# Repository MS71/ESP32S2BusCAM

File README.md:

# ESP32S2BusCAM

Fetures:
* ESP32 S2/S3 Mini Modul mit und ohne PSRAM
* USB Micro Port
* JTAG Stecker
* ESP Prog Stecker
* Micro SDCard Slot
* 22 Pin Camera Stecker, Camera wird auf das ESP32 Modul geklappt
* Spannungs Regler für Ext Versorgung
* SPI/I2C Bus Stecker
* Support für Stereo Quad Camara
* 4 Pin OLED Display
* IR LEDs
* Debug LEDs

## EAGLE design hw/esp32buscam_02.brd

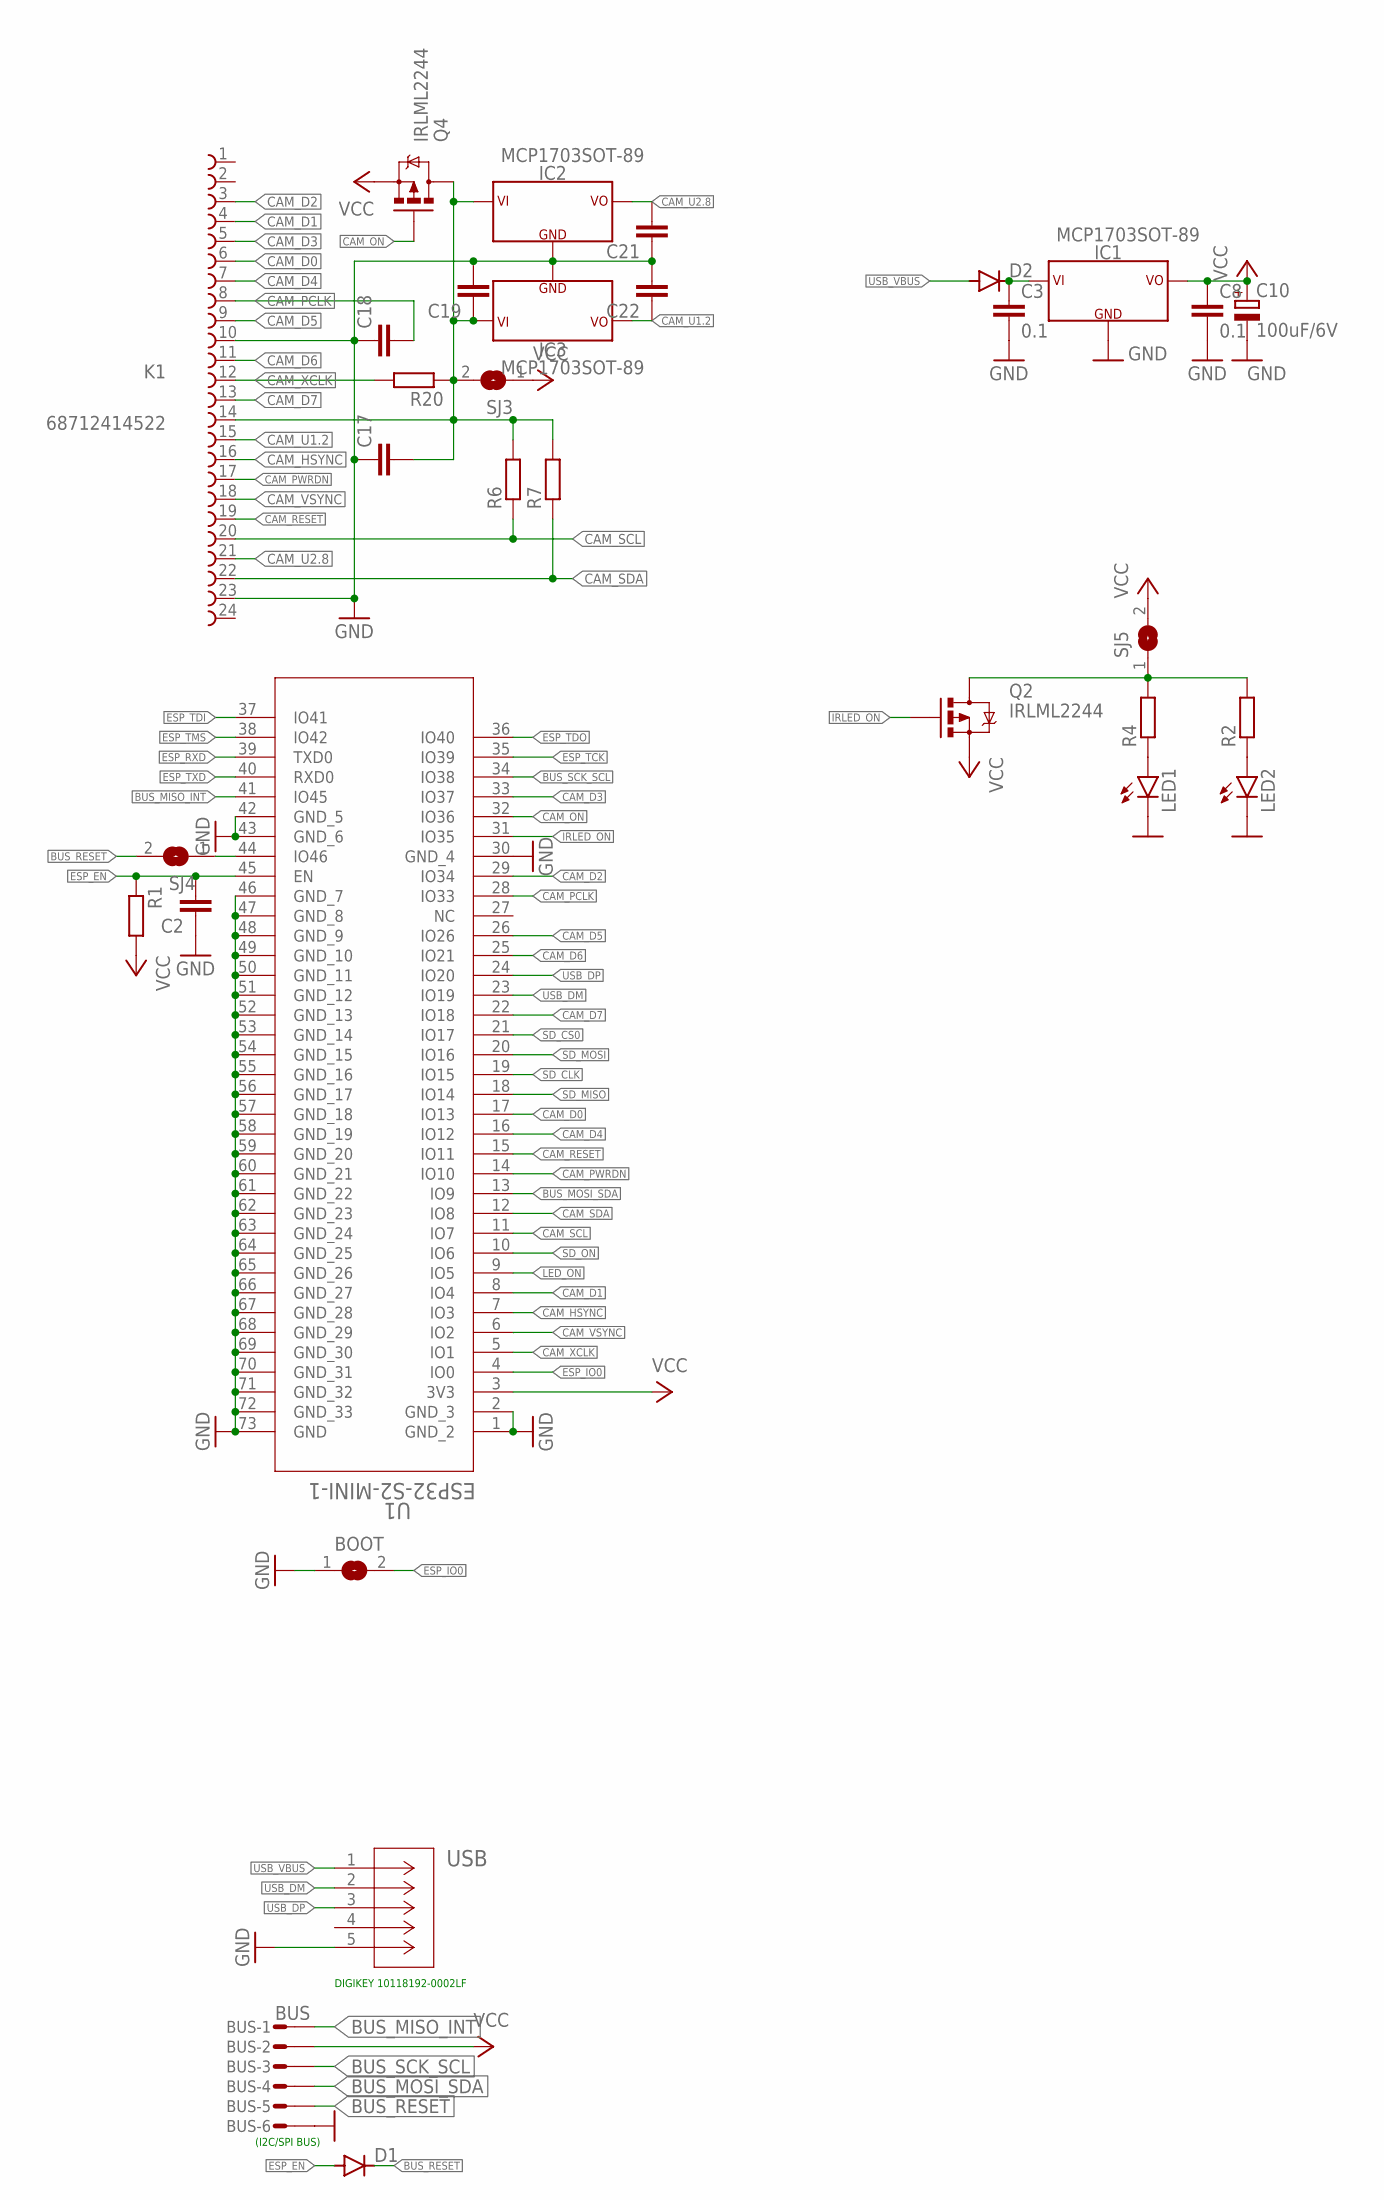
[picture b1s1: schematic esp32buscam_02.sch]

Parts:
BOOT: SJ
BUS: BUS; MICROMATCH-6SMD
C2, C17, C18, C19, C21, C22: C-EUC0603; C0603
C3, C8: 0.1; C0805
C10: 100uF/6V; B/3528-21R
D1, D2: DIODE-MINIMELF; MINIMELF
IC1, IC2, IC3: MCP1703SOT-89; SOT89
K1: 68712414522
LED1, LED2: LED5MM
Q2, Q4: IRLML2244; SOT23-3
R1, R6, R7, R20: R-EU_R0603; R0603
R2, R4: R-EU_R0402; R0402
SJ3, SJ4, SJ5: SJ
U1: ESP32-S2-MINI-1; QFN60_ESP32-S2-MINI-1_EXP
USB: 10118192-0002LF; CONN_10118192-0002LF_AMP

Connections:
BUS_MISO_INT: BUS.1, U1.41 (IO45)
BUS_MOSI_SDA: BUS.4, U1.13 (IO9)
BUS_RESET: BUS.5, D1.C, SJ4.2
BUS_SCK_SCL: BUS.3, U1.34 (IO38)
CAM_D0: K1.6, U1.17 (IO13)
CAM_D1: K1.4, U1.8 (IO4)
CAM_D2: K1.3, U1.29 (IO34)
CAM_D3: K1.5, U1.33 (IO37)
CAM_D4: K1.7, U1.16 (IO12)
CAM_D5: K1.9, U1.26 (IO26)
CAM_D6: K1.11, U1.25 (IO21)
CAM_D7: K1.13, U1.22 (IO18)
CAM_HSYNC: K1.16, U1.7 (IO3)
CAM_ON: Q4.1 (G), U1.32 (IO36)
CAM_PCLK: C18.2, K1.8, U1.28 (IO33)
CAM_PWRDN: K1.17, U1.14 (IO10)
CAM_RESET: K1.19, U1.15 (IO11)
CAM_SCL: K1.20, R6.1, U1.11 (IO7)
CAM_SDA: K1.22, R7.1, U1.12 (IO8)
CAM_U1.2: C22.1, IC3.3 (VCC), K1.15
CAM_U2.8: C21.2, IC2.3 (VCC), K1.21
CAM_VSYNC: K1.18, U1.6 (IO2)
CAM_XCLK: K1.12, R20.2, U1.5 (IO1)
ESP_EN: C2.2, D1.A, R1.1, U1.45 (EN)
ESP_IO0: BOOT.2, U1.4 (IO0)
ESP_RXD: U1.39 (TXD0)
ESP_TCK: U1.35 (IO39)
ESP_TDI: U1.37 (IO41)
ESP_TDO: U1.36 (IO40)
ESP_TMS: U1.38 (IO42)
ESP_TXD: U1.40 (RXD0)
GND: BOOT.1, BUS.6, C2.1, C3.2, C8.2, C10.-, C17.1, C18.1, C19.2, C21.1, C22.2, IC1.1 (GND), IC2.1 (GND), IC3.1 (GND), K1.10, K1.23, LED1.K (C), LED2.K (C), U1.1 (GND_2), U1.2 (GND_3), U1.30 (GND_4), U1.42 (GND_5), U1.43 (GND_6), U1.46 (GND_7), U1.47 (GND_8), U1.48 (GND_9), U1.49 (GND_10), U1.50 (GND_11), U1.51 (GND_12), U1.52 (GND_13), U1.53 (GND_14), U1.54 (GND_15), U1.55 (GND_16), U1.56 (GND_17), U1.57 (GND_18), U1.58 (GND_19), U1.59 (GND_20), U1.60 (GND_21), U1.61 (GND_22), U1.62 (GND_23), U1.63 (GND_24), U1.64 (GND_25), U1.65 (GND_26), U1.66 (GND_27), U1.67 (GND_28), U1.68 (GND_29), U1.69 (GND_30), U1.70 (GND_31), U1.71 (GND_32), U1.72 (GND_33), U1.73 (GND), USB.5; also elsewhere on the board
IRLED_ON: Q2.1 (G), U1.31 (IO35)
LED_ON: U1.9 (IO5)
unnamed: LED1.A, R4.1
unnamed: SJ4.1, U1.44 (IO46)
unnamed: LED2.A, R2.1
unnamed: Q2.3 (D), R2.2, R4.2, SJ5.1
SD_CLK: U1.19 (IO15)
SD_CS0: U1.21 (IO17)
SD_MISO: U1.18 (IO14)
SD_MOSI: U1.20 (IO16)
SD_ON: U1.10 (IO6)
USB_DM: U1.23 (IO19), USB.2
USB_DP: U1.24 (IO20), USB.3
USB_VBUS: D2.A, USB.1
V: C3.1, D2.C, IC1.2 (VIN), IC1.4 (VIN); also elsewhere on the board
VCC: BUS.2, C8.1, C10.+, IC1.3 (VCC), Q2.2 (S), Q4.2 (S), R1.2, SJ3.1, SJ5.2, U1.3 (3V3)
VCC_CAM: C17.2, C19.1, IC2.2 (VIN), IC2.4 (VIN), IC3.2 (VIN), IC3.4 (VIN), K1.14, Q4.3 (D), R6.2, R7.2, R20.1, SJ3.2

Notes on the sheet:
DIGIKEY 10118192-0002LF
(I2C/SPI BUS)

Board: 2 copper layers, 35 parts (17 on the bottom side), 38 nets, no tracks yet.

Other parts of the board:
D3: MINIMELF
PAD5, PAD6: 1,6/0,9

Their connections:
GND: PAD6.1; also elsewhere on the board
V: D3.C; also elsewhere on the board
VEXT: D3.A, PAD5.1

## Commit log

2021-08-29 first 100% layout

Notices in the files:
parts and their libraries:
FPC_Connectors_Flat_Flexible_Cable_rev15: Copyright: Würth Elektronik
User-Submitted: Licensing: Creative Commons ShareAlike 4.0 International - https://creativecommons.org/licenses/by-sa/4.0
COPYRIGHT: Copyright (C) 2018 Accelerated Designs. All rights reserved
